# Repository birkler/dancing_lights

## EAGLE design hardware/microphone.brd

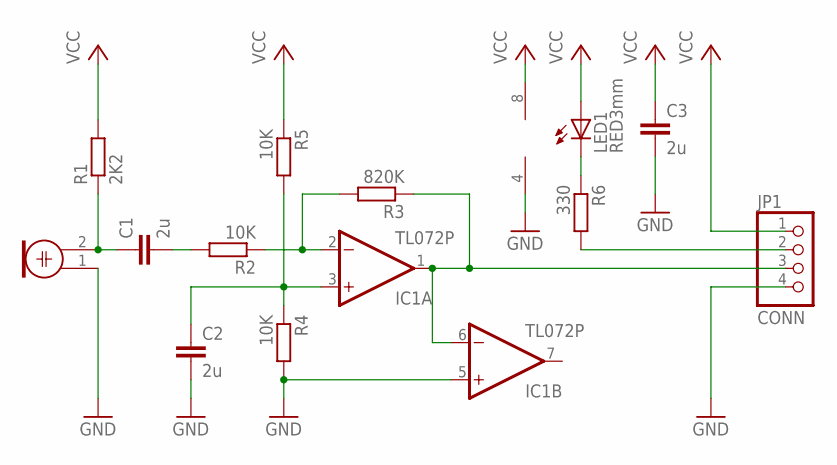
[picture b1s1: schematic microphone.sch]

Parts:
C1: 2u; C050-025X075
C2: 2u; C025-025X050
C3: 2u; C075-032X103
IC1: TL072P; DIL08
JP1: CONN; 1X04
LED1: RED3mm; LED5MM
M1: ELECTRET_MICROPHON-F6035AP; F6035AP
R1: 2K2; 0204/7
R2, R4: 10K; 0204V
R3: 820K; 0204V
R5: 10K; 0204/7
R6: 330; 0204/7

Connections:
AMP_OUT: IC1.1 (OUT), IC1.6 (-IN), JP1.3, R3.1
GND: C2.2, C3.2, IC1.4 (V-), IC1.5 (+IN), JP1.4, M1.1, R4.2
LED_IN: JP1.2, R6.2
LED_IN_: LED1.K (C), R6.1
MIC_IN_BIAS: C1.2, R2.2
MIC_OUT: C1.1, M1.2, R1.1
OP+: C2.1, IC1.3 (+IN), R4.1, R5.2
OP-: IC1.2 (-IN), R2.1, R3.2
VCC: C3.1, IC1.8 (V+), JP1.1, LED1.A, R1.2, R5.1

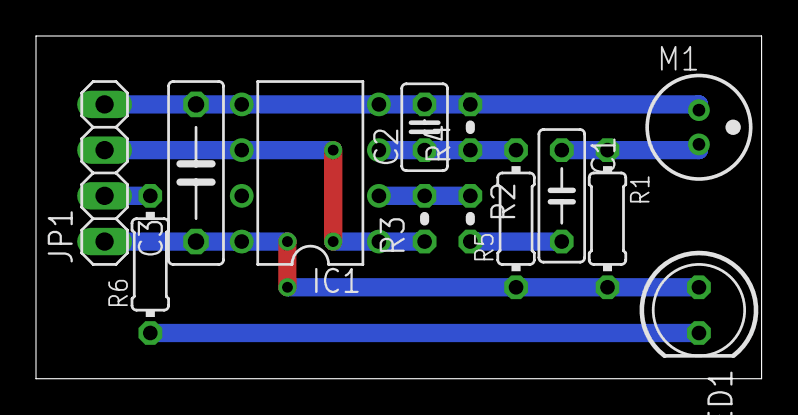
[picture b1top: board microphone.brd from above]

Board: 2 copper layers, 40.3 x 19.0 mm, 13 parts (0 on the bottom side), 9 nets.

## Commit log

2016-11-10 inital commit. pot value can control APA102C strip.
2016-11-10 update with schematics.
